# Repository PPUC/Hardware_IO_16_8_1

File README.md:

# Standard IO PCB for PPUC Project
This is the hardware for a standard IO card which was designed for the PPUC pinball project, but can be useful in other applications as well.
It is designed for being low cost and functional for experimental use.  
Not everything is tested nor does it fulfill EMC or any other specifications.  
Use at your own risk!
To make use of anything of this project a basic understanding of electronics and programming is necessary. Nothing of it is "plug and play". I'm surely not liable for any damage to assemblies, pinball machines or even persons.

## Picture of the Board

## Name
IO_16_8_1 as it has 16 inputs, 8 outputs and one special output.  
Actually the inputs can also be used as outputs (see later in this document).

## Power Supply
The IO card must be supplied by 5 V (+-0.5 V) for logic and inputs. Additionally nominal 48 V for high power outputs. As these outputs are open drain, the voltage can actually be up to 60 V. In the circuit diagram the voltage is called 48 V.

## Controller
A RP2040 is used for it's cost/performance ratio. It is the same controller that is used in the Raspberry Pi Pico.

## Communication Interfaces
* RS_485: main communication interface for controlling outputs and scan inputs. Usually connected to a host interface like a PC or Raspberry Pi or similar.
* USB C: for programming, debug and flashing
* Serial Wire: alternative for programming, debug and flashing
* IIC: the PCB can be populated with an QWIIC connector (normally not mounted). This can be used for connecting to other PCBs or experimental use. It uses the same UART as for the RS485.
* UART, I2C, SPI: instead of using the input pins for inputs they can also be used as an additional interface (see docu of RP2040 for pins and function). Speed up to 10 kHz should be possible (100 kHz for In_2 and In_3).

## Switches (on board)
* Reset: hardware reset for controller (RP2040)
* Boot: if active the board connects to a PC like an USB stick. Usually used for programming the code into the flash memory on the board.
* DIP-switches: usually used to select an address for RS485 (16 combinations)

## Inputs (and low power outputs)
The 16 inputs are used for reading the state of an external switch. The switch is normally connected to ground (GND). Internally the input is pulled up to 5 V by a 10k resistor.

All inputs can also be used as signal-outputs (if programmed accordingly). The output is internally pulled up by a 10k resistor to 5 V. A higher voltage can be applied externally (max. 30 V) but be sure to have your hardware and software! setup correctly as no protection for damage is provided in that case. A maximum of 2 mA can be sinked/sourced.

The inputs In_2 and In_3 are designed for higher speed (100 kHz). The Pull-Up can be soldered to other pads to be pulled to 3,3 V (instead of 5 V). An input capacitance can be added (soldered) for better noise immunity but lower speed. Since version 1.0.1 the caps are soldered by default and must be removed if a high-speed serial connection is needed.

The input terminals can also be "miss"used for a switch matrix. To do that (no matter if used as column or row) the input resistor (330 Ohm) must be short cut (or replaced by a zero Ohm type). Background: the 330 Ohm resistor protects the circuit if the terminal is used as an output and accidentally a short cut is done at the terminal. Unfortunately the low voltage value gets too high when used in a switch matrix (diode voltage plus voltage drop due to added up currents through the resistor). This happens when more switches are closed at the same time.  
Having said that, there is an exception: if you use the Terminals 13 to 16 (mid power) as your drivers (strobe signal) then you don't need to change anything. That gives you for example a 4x4 or 8x4 matrix. You can also always use the specially designed PCB "Hardware_IO_16x8_matrix" for your switch matrix.

The inputs In_13 to In_16 have an additional open drain output transistor that allows higher currents in case of being used as an output (up to 3 A at 25 °C ambient temperature). The outputs are internally pulled up by a 10k resistor to 5 V. A higher voltage (max. 30 V) can be applied externally but be sure to have your hardware and software! setup correctly as no protection for damage is provided in that case. Please be aware that the default state (before software takes over control) is "on".  
If used as input In_13 to In_16 feature a memory (similar to a relay self-holding function). If the input has ever seen a low signal (e.g. switch closed to GND) it will stay that way until it gets an active high signal from the RP2040 (make the corresponding pin an output with signal "high" and then make it an input again). If this behavior is not wanted you can lift pin 3 of Q13 to Q16, then you have an input/output like e.g. terminal 1 with static behavior but no additional output power.  
Why not keep it simple and make all inputs the same? To give the choice to use the terminals as outputs (mid-power) as in pinball use case, there are often too many inputs and a lack on outputs. Therefore an output transistor to 4 of the I/O pins were added to be able to switch more power. As an side effect if this terminal is configured as an input it has this memory or self-holding characteristic (once triggered stays triggered). This can be dealt with by software, in a way that it actually acts like a normal input. In the end you have the benefit of mid-power-output but the drawback that the software getting more complex for the use case of a "normal" input.  
If you use the PPUC software and you have configured the terminal as an input, it acts like a normal input and you don't have to care about it.

Here is an example what software steps are needed for normal input configuration, e.g. for IN_14:
1. find the corresponding GPIO for IN_14: that is GPIO16 at the physical Pin 27 of RP2040
2. set GPIO16 as output and set it to "high".
3. configure the GPIO16 as an input (now it is an input that is "low active", therefore setup for a switch to ground)
4. if a low at the terminal IN_14 appears, the GPIO16 will be read as "low" and stays that way even if the switch on terminal IN_14 opens again (self-holding)
5. when you think it's time to reactivate the input ("arm the input"), then goto 2.

If you do 5. always right after the input read "low" than it looks like a normal input without self-holding characteristic.

## High Power Outputs
There are 8 high power outputs available. Usually they are connected to pinball solenoids or flashers. A recovery diode for the solenoids is placed on the pcb, so no need for diodes at the coils. The outputs are open drain and drive currents up to 20 A with a load connected to a voltage of up to 60 V. Be aware that the current is limited by the fuse F2. It will blow within about 1 s at 20 A. You might use a 10 A fuse if necessary.

It's recommended to use 2 wires (back and forth) for each solenoid. That improves the EMC a lot.

## Special Output
One special output is available for high speed signals. The voltage is 5 V, it is a push pull output that can drive a current up to 8 mA. It can be used to e.g. control a WS2812 LED strip.

## Terminal Blocks, Connectors
The PCB holes are designed to take different manufacturers of 6 pin terminal blocks. Be sure to use terminal blocks with a pitch of 3.5 mm. There is some additional space at the front and back of the terminal blocks to accommodate different sizes (e.g., Dinkle and Phoenix Contact). Some no-name manufacturers from China are also already in use. The direct clamping blocks are the least expensive but please also consider using plug-in terminals for easy maintenance (see picture below).

## Recommendations
* Connect only one Flipper to a pcb if possible. The advantage is, that all the energy of the big capacitor is available for the flipper, which is usually the solenoid with the highest current. If you have more flipper fingers than PCBs then spread the flipper solenoids as even as possible across the PCBs (e.g. if you have 6 flipper fingers it's better to connect 2 per board instead of all 6 at one board).
* Wire related switches and solenoids for fast flip devices (e.g. flipper, bumper, sling, kick back) to the same pcb. Then you can archive the shortest possible time lag between activating the switch and firing the solenoid.
* RS485 termination: short JP2 at the end of the RS485 bus. There should also be a 120 Ohm resistor at the beginning of the bus (e.g. USB to RS485 adapter).
* RS485 biasing: short JP1 and JP3 exactly once at any point of the RS485 bus. Only do this if no bias resistors are installed on the USB to RS485 adapter. 
* It's recommended to use flipper coils for higher voltage (like 40 - 50 V) as they draw less current. Since Version 1.1.1 low resistance coils (designed for 24 V) should work as well. You should also change the fuse F2 to 10 A for that application.
* If the MOSFETs on the high power outputs are not available (or you want to use the big player brands) here are some alternatives (I haven't tested any of them, but they should work according to their specification): GL40N10A4 (seems to be the same as NCE0140KA), RD3P200SNFRA, NVD6824NL, IPD90N10S4L-06, LSGG10R085W3

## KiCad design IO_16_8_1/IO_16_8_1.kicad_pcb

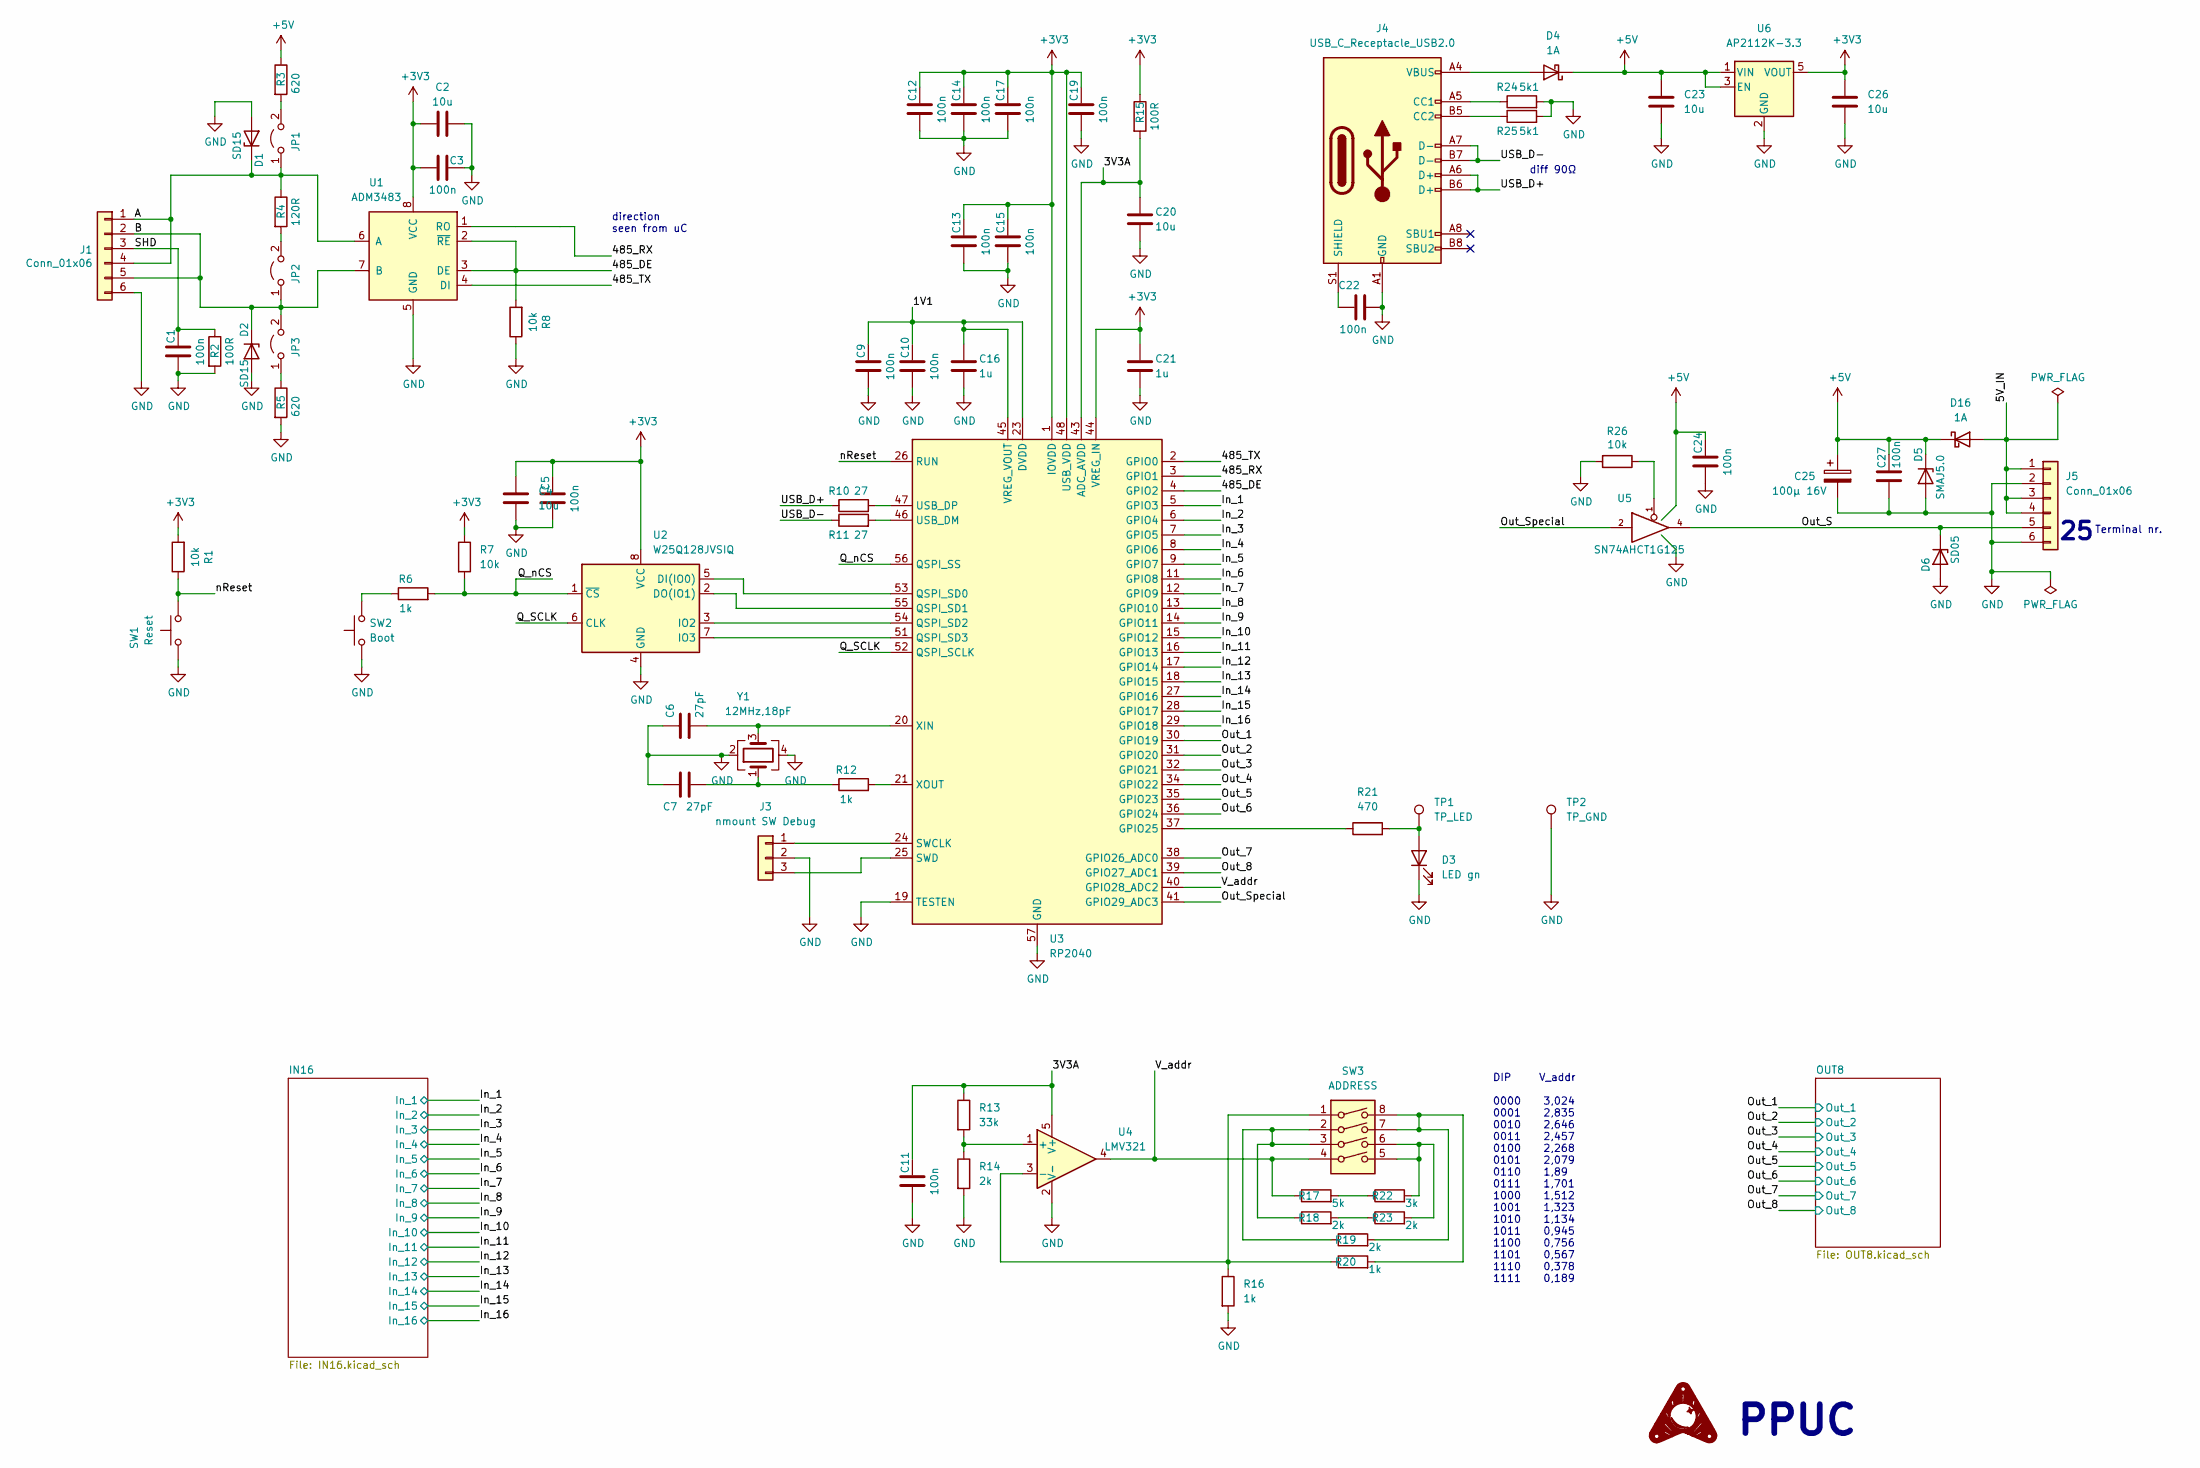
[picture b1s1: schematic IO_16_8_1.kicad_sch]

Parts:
C1, C3, C5, C9, C10, C11, C12, C13, C14, C15, C17, C19, C22, C24, C27: 100n; C_0402_1005Metric
C2, C4, C20, C23, C26: 10u; C_0603_1608Metric
C6, C7: 27pF; C_0402_1005Metric
C16, C21: 1u; C_0402_1005Metric
C25: 100µ 16V; CP_Elec_6.3x5.4; JLCPCB Rotation Offset 180
D1, D2: SD15; D_SOD-323
D3: LED gn; LED_0805_2012Metric
D4, D16: 1A; D_SOD-323
D5: SMAJ5.0; D_SMA
D6: SD05; D_SOD-323
J1, J5: Conn_01x06; Terminal_Block_RTMPin
J3: nmount SW Debug; PinSocket_1x03_P2.54mm_Vertical
J4: USB_C_Receptacle_USB2.0; USB_C_Receptacle_XKB_U262-16XN-4BVC11
JP1, JP2, JP3: Jumper_2_Open; PinHeader_1x02_P2.54mm_Vertical
R1, R7, R8, R26: 10k; R_0603_1608Metric
R2, R15: 100R; R_0603_1608Metric
R3, R5: 620; R_0402_1005Metric
R4: 120R; R_0603_1608Metric
R6, R12, R16, R20: 1k; R_0402_1005Metric
R10, R11: 27; R_0402_1005Metric
R13: 33k; R_0603_1608Metric
R14, R18, R19, R23: 2k; R_0603_1608Metric
R17: 5k; R_0603_1608Metric
R21: 470; R_0603_1608Metric
R22: 3k; R_0603_1608Metric
R24, R25: 5k1; R_0603_1608Metric
SW1: Reset; SW_SPST_SKQG_WithStem
SW2: Boot; SW_SPST_SKQG_WithStem
SW3: ADDRESS; SW_DIP_SPSTx04_Slide_6.7x11.72mm_W8.61mm_P2.54mm_LowProfile; JLCPCB Rotation Offset 90
TP1: TP_LED; Pin_D1.0mm_L10.0mm
TP2: TP_GND; Pin_D1.0mm_L10.0mm
U1: ADM3483; SOIC-8_3.9x4.9mm_P1.27mm
U2: W25Q128JVSIQ; SOIC-8_5.23x5.23mm_P1.27mm
U3: RP2040; QFN-56-1EP_7x7mm_P0.4mm_EP3.2x3.2mm; JLCPCB Rotation Offset -90
U4: LMV321; SOT-23-5
U5: SN74AHCT1G125; SOT-23-5
U6: AP2112K-3.3; SOT-23-5; JLCPCB Rotation Offset 90
Y1: 12MHz,18pF; Crystal_SMD_3225-4Pin_3.2x2.5mm

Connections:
+3V3: C2.1, C3.1, C4.1, C5.1, C12.1, C13.1, C14.1, C15.1, C17.1, C19.1, C21.1, C26.1, R1.2, R7.1, R15.1, U1.8 (VCC), U2.8 (VCC), U3.1 (IOVDD), U3.10 (IOVDD), U3.22 (IOVDD), U3.33 (IOVDD), U3.42 (IOVDD), U3.44 (VREG_IN), U3.48 (USB_VDD), U3.49 (IOVDD), U6.5 (VOUT); also elsewhere on the board
+5V: C23.1, C24.1, C25.1, C27.1, D4.1 (K), D5.1 (K), D16.1 (K), R3.1, U5.5 (VCC), U6.1 (VIN), U6.3 (EN); also elsewhere on the board
/1V1: C9.1, C10.1, C16.1, U3.23 (DVDD), U3.45 (VREG_VOUT), U3.50 (DVDD)
/3V3A: C11.1, C20.1, R13.1, R15.2, U3.43 (ADC_AVDD), U4.5 (V+)
/485_DE: R8.2, U1.2 (~RE), U1.3 (DE), U3.4 (GPIO2)
/485_RX: U1.1 (RO), U3.3 (GPIO1)
/485_TX: U1.4 (DI), U3.2 (GPIO0)
/A: D1.1 (K), J1.1, J1.4, JP1.1 (A), R4.1, U1.6 (A)
/B: D2.1 (K), J1.2, J1.5, JP2.1 (A), JP3.2 (B), U1.7 (B)
/In_1: U3.5 (GPIO3); also elsewhere on the board
/In_2: U3.6 (GPIO4); also elsewhere on the board
/In_3: U3.7 (GPIO5); also elsewhere on the board
/In_4: U3.8 (GPIO6); also elsewhere on the board
/In_5: U3.9 (GPIO7); also elsewhere on the board
/In_6: U3.11 (GPIO8); also elsewhere on the board
/In_7: U3.12 (GPIO9); also elsewhere on the board
/In_8: U3.13 (GPIO10); also elsewhere on the board
/In_9: U3.14 (GPIO11); also elsewhere on the board
/In_10: U3.15 (GPIO12); also elsewhere on the board
/In_11: U3.16 (GPIO13); also elsewhere on the board
/In_12: U3.17 (GPIO14); also elsewhere on the board
/In_13: U3.18 (GPIO15); also elsewhere on the board
/In_14: U3.27 (GPIO16); also elsewhere on the board
/In_15: U3.28 (GPIO17); also elsewhere on the board
/In_16: U3.29 (GPIO18); also elsewhere on the board
/Out_1: U3.30 (GPIO19); also elsewhere on the board
/Out_2: U3.31 (GPIO20); also elsewhere on the board
/Out_3: U3.32 (GPIO21); also elsewhere on the board
/Out_4: U3.34 (GPIO22); also elsewhere on the board
/Out_5: U3.35 (GPIO23); also elsewhere on the board
/Out_6: U3.36 (GPIO24); also elsewhere on the board
/Out_7: U3.38 (GPIO26_ADC0); also elsewhere on the board
/Out_8: U3.39 (GPIO27_ADC1); also elsewhere on the board
/Out_S: D6.1 (K), J5.5, U5.4
/Out_Special: U3.41 (GPIO29_ADC3), U5.2
/Q_SCLK: U2.6 (CLK), U3.52 (QSPI_SCLK)
/Q_nCS: R6.2, R7.2, U2.1 (~CS), U3.56 (QSPI_SS)
/SHD: C1.1, J1.3, R2.1
/USB_D+: J4.A6 (D+), J4.B6 (D+), R10.1
/USB_D-: J4.A7 (D-), J4.B7 (D-), R11.1
/V_addr: R17.1, SW3.4, U3.40 (GPIO28_ADC2), U4.4
/nReset: R1.1, SW1.2, U3.26 (RUN)
unnamed: C6.2, U3.20 (XIN), Y1.3
unnamed: C7.2, R12.1, Y1.1
unnamed: C22.1, J4.S1 (SHIELD)
unnamed: D3.2 (A), R21.2, TP1.1
unnamed: D4.2 (A), J4.A4 (VBUS), J4.A9 (VBUS), J4.B4 (VBUS), J4.B9 (VBUS)
unnamed: J3.1, U3.24 (SWCLK)
unnamed: J3.3, U3.25 (SWD)
unnamed: J4.A5 (CC1), R24.1
unnamed: J4.B5 (CC2), R25.1
unnamed: JP1.2 (B), R3.2
unnamed: JP2.2 (B), R4.2
unnamed: JP3.1 (A), R5.1
unnamed: R6.1, SW2.2
unnamed: R10.2, U3.47 (USB_DP)
unnamed: R11.2, U3.46 (USB_DM)
unnamed: R12.2, U3.21 (XOUT)
unnamed: R13.2, R14.1, U4.1 (+)
unnamed: R16.1, R20.1, SW3.1, U4.3 (-)
unnamed: R17.2, R22.1
unnamed: R18.1, R19.1, SW3.2, SW3.3
unnamed: R18.2, R23.1
unnamed: R19.2, R20.2, SW3.7, SW3.8
unnamed: R21.1, U3.37 (GPIO25)
unnamed: R22.2, R23.2, SW3.5, SW3.6
unnamed: R26.1, U5.1
unnamed: U2.2 (DO(IO1)), U3.55 (QSPI_SD1)
unnamed: U2.3 (IO2), U3.54 (QSPI_SD2)
unnamed: U2.5 (DI(IO0)), U3.53 (QSPI_SD0)
unnamed: U2.7 (IO3), U3.51 (QSPI_SD3)

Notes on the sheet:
diff 90Ω
DIP V_addr 0000 3,024 0001 2,835 0010 2,646 0011 2,457 0100 2,268 0101 2,079 0110 1,89 0111 1,701 1000 1,512 1001 1,323 1010 1,134 1011 0,945 1100 0,756 1101 0,567 1110 0,378 1111 0,189
direction seen from uC
Terminal nr.
PPUC

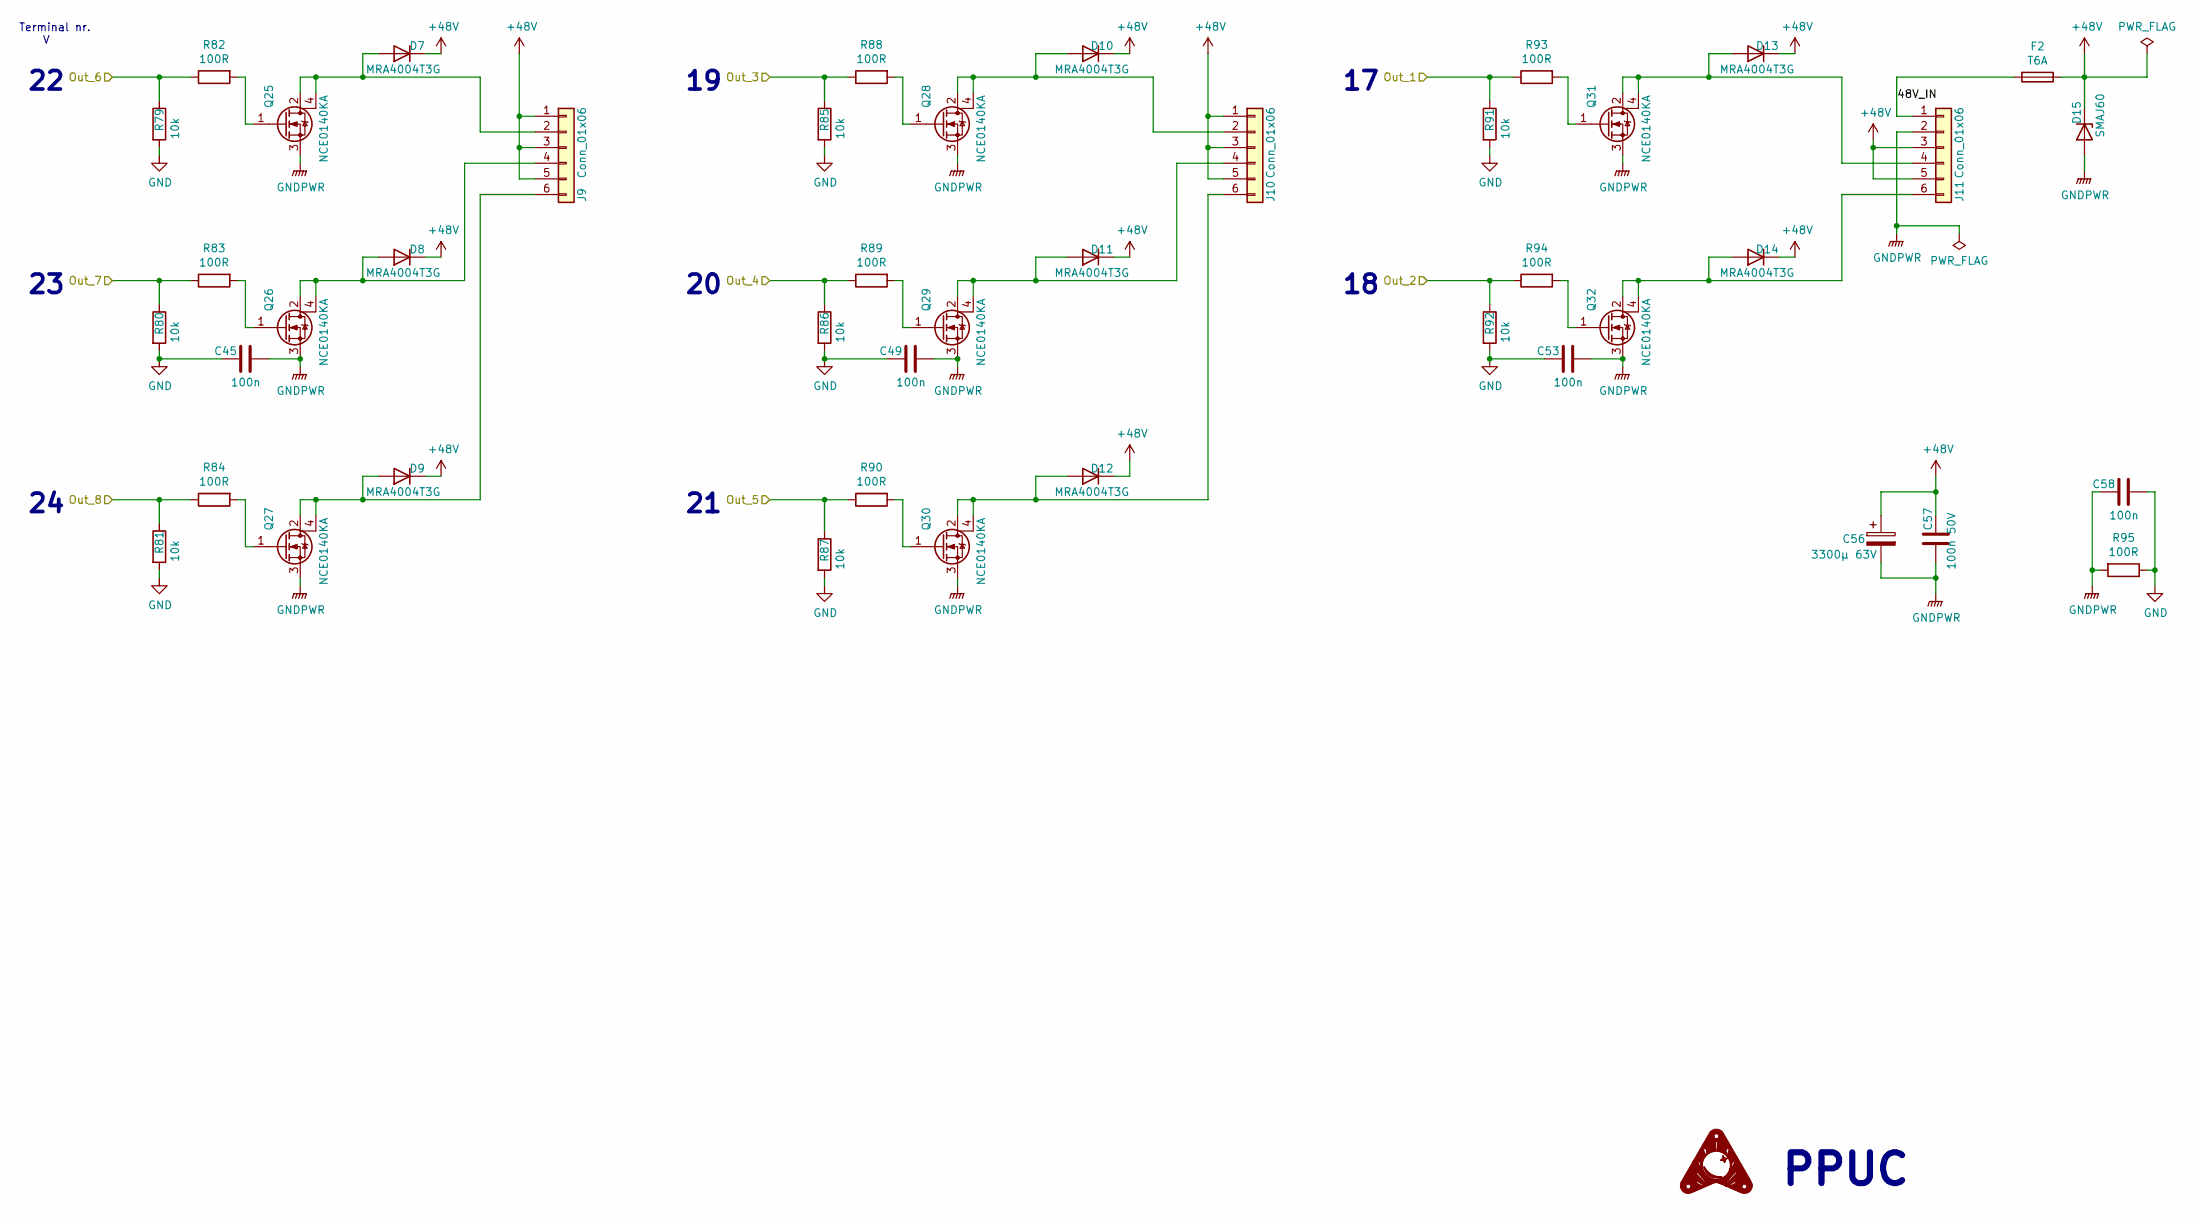
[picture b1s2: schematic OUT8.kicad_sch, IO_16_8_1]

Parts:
C45, C49, C53, C58: 100n; C_0402_1005Metric
C56: 3300µ 63V; CP_Radial_D30.0mm_P10.00mm_SnapIn
C57: 100n 50V; C_0603_1608Metric
D7, D8, D9, D10, D11, D12, D13, D14: MRA4004T3G; D_SMA
D15: SMAJ60; D_SMA
F2: T6A; Fuseholder_Cylinder-5x20mm_Schurter_0031_8201_Horizontal_Op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
J9, J10, J11: Conn_01x06; Terminal_Block_RTMPin
Q25, Q26, Q27, Q28, Q29, Q30, Q31, Q32: NCE0140KA; TO-252-3_TabPin4
R79, R80, R81, R85, R86, R87, R91, R92: 10k; R_0603_1608Metric
R82, R83, R84, R88, R89, R90, R93, R94, R95: 100R; R_0603_1608Metric

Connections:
/OUT8/48V_IN: F2.2, J11.1
/Out_1: R91.1, R93.1; also elsewhere on the board
/Out_2: R92.1, R94.1; also elsewhere on the board
/Out_3: R85.1, R88.1; also elsewhere on the board
/Out_4: R86.1, R89.1; also elsewhere on the board
/Out_5: R87.1, R90.1; also elsewhere on the board
/Out_6: R79.1, R82.1; also elsewhere on the board
/Out_7: R80.1, R83.1; also elsewhere on the board
/Out_8: R81.1, R84.1; also elsewhere on the board
unnamed: D7.2 (A), J9.2, Q25.2 (D), Q25.4 (D)
unnamed: D8.2 (A), J9.4, Q26.2 (D), Q26.4 (D)
unnamed: D9.2 (A), J9.6, Q27.2 (D), Q27.4 (D)
unnamed: D10.2 (A), J10.2, Q28.2 (D), Q28.4 (D)
unnamed: D11.2 (A), J10.4, Q29.2 (D), Q29.4 (D)
unnamed: D12.2 (A), J10.6, Q30.2 (D), Q30.4 (D)
unnamed: D13.2 (A), J11.4, Q31.2 (D), Q31.4 (D)
unnamed: D14.2 (A), J11.6, Q32.2 (D), Q32.4 (D)
unnamed: Q25.1 (G), R82.2
unnamed: Q26.1 (G), R83.2
unnamed: Q27.1 (G), R84.2
unnamed: Q28.1 (G), R88.2
unnamed: Q29.1 (G), R89.2
unnamed: Q30.1 (G), R90.2
unnamed: Q31.1 (G), R93.2
unnamed: Q32.1 (G), R94.2

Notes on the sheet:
Terminal nr. V
PPUC

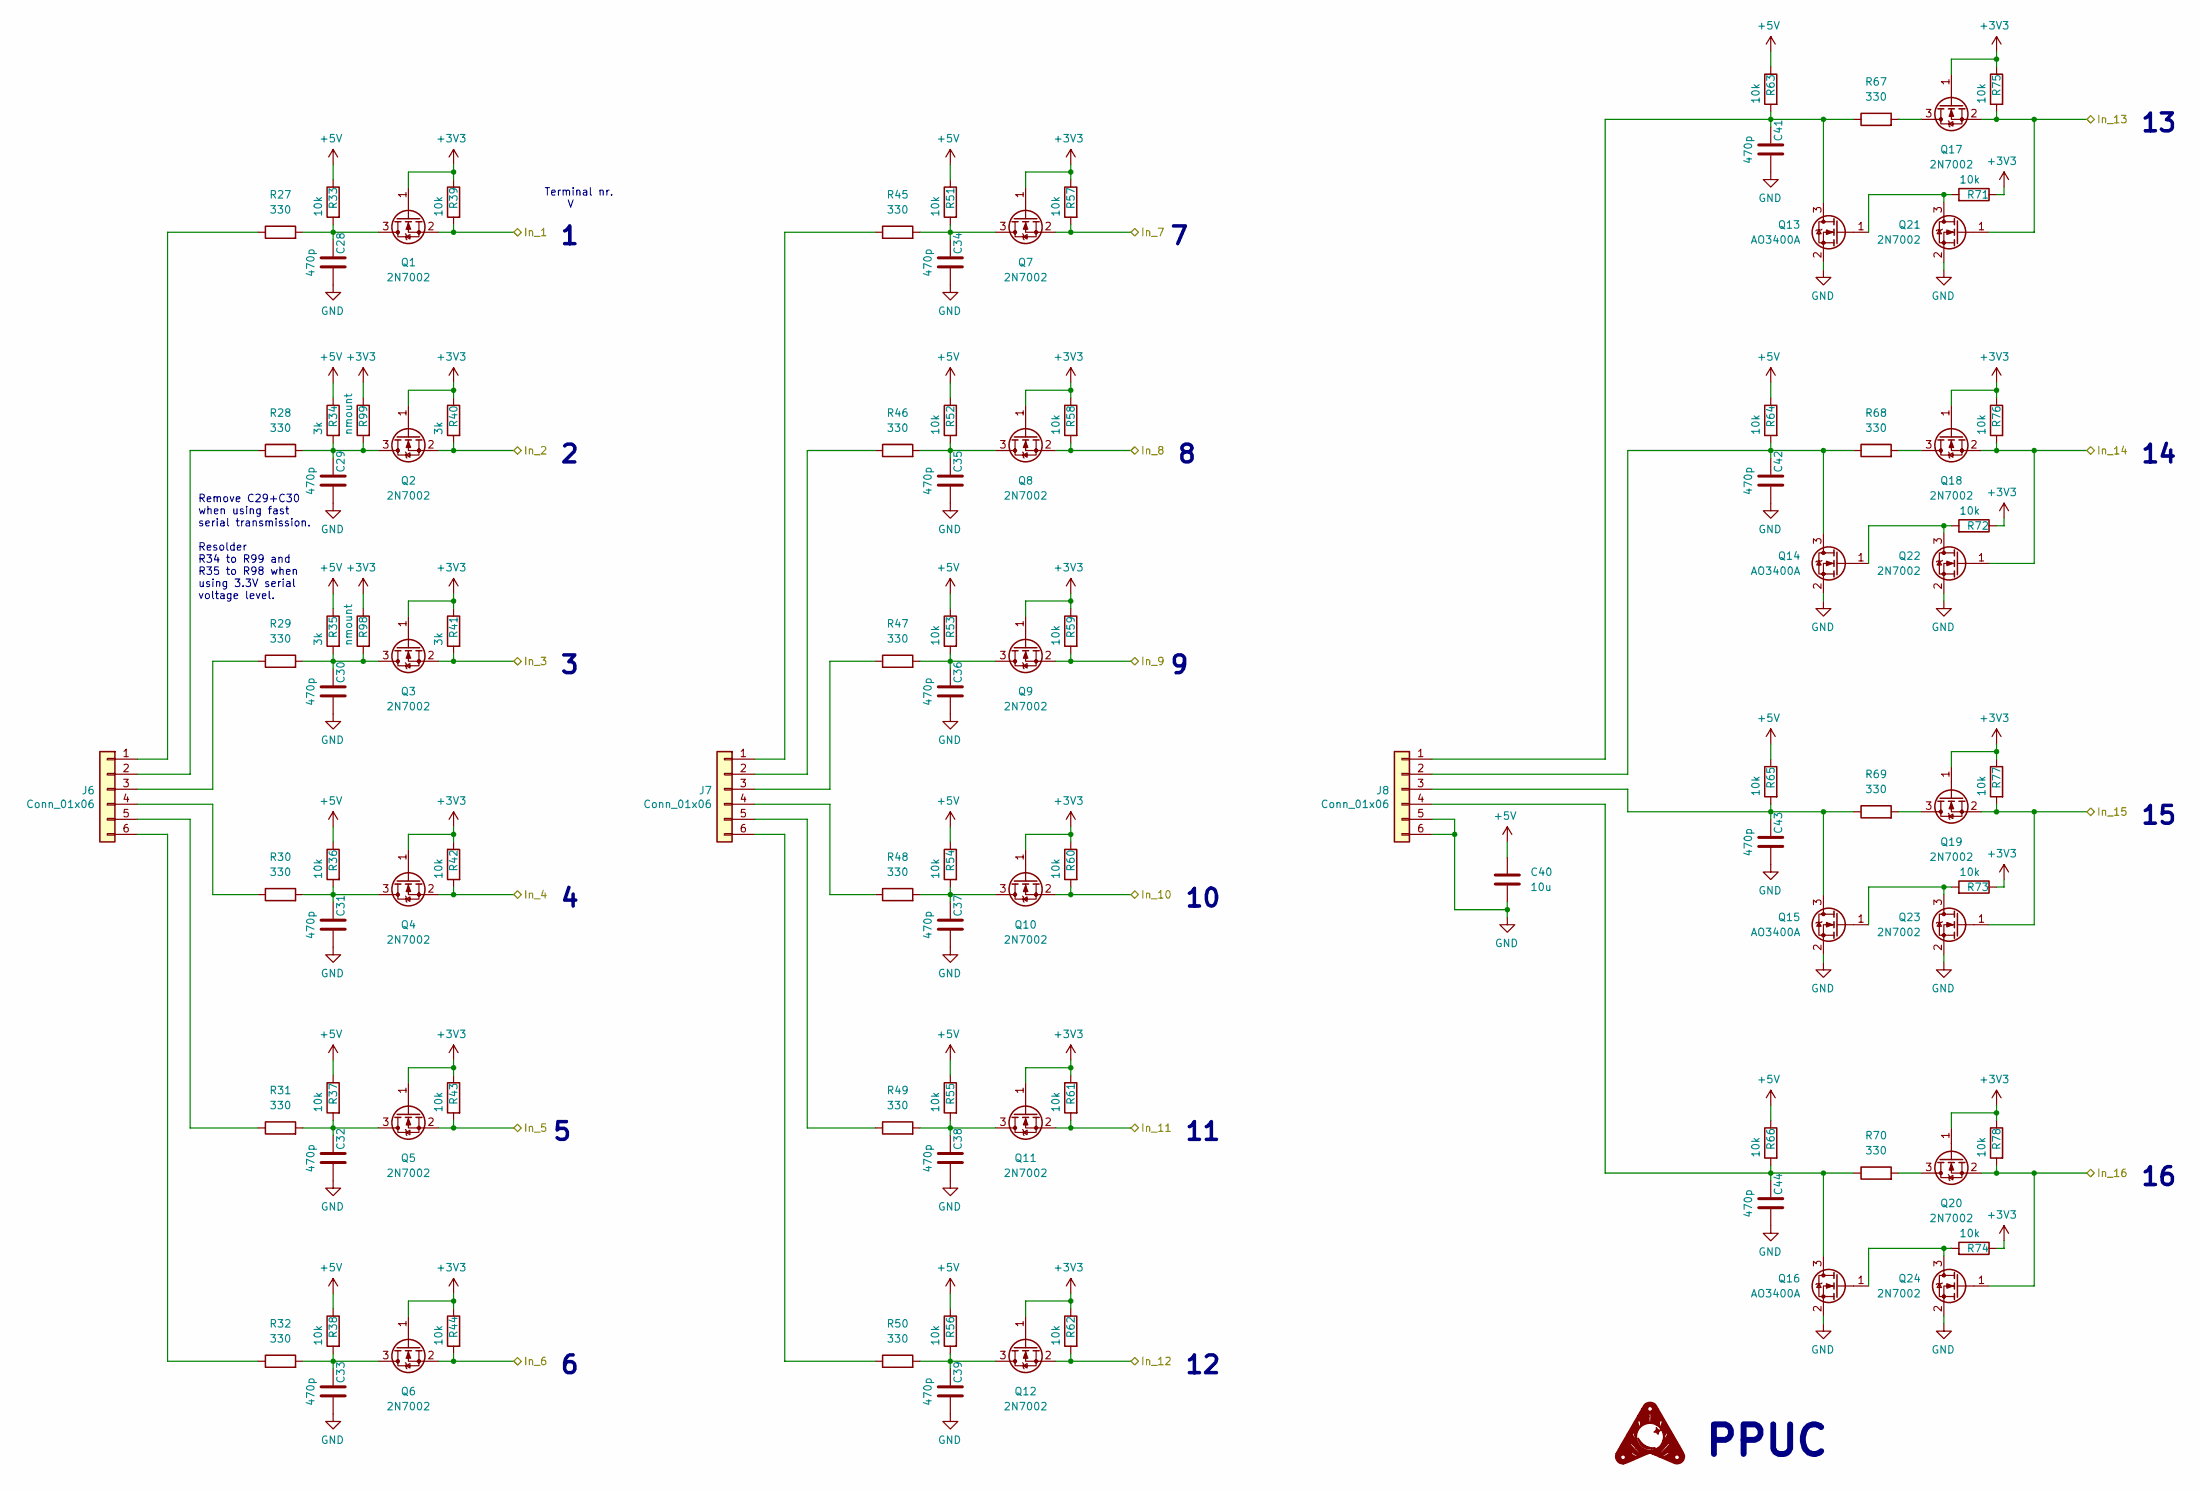
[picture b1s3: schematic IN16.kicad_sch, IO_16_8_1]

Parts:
C28, C29, C30, C31, C32, C33, C34, C35, C36, C37, C38, C39, C41, C42, C43, C44: 470p; C_0603_1608Metric
C40: 10u; C_0603_1608Metric
J6, J7, J8: Conn_01x06; Terminal_Block_RTMPin
Q1, Q2, Q3, Q4, Q5, Q6, Q7, Q8, Q9, Q10, Q11, Q12, Q17, Q18, Q19, Q20, Q21, Q22, Q23, Q24: 2N7002; SOT-23
Q13, Q14, Q15, Q16: AO3400A; SOT-23
R27, R28, R29, R30, R31, R32, R45, R46, R47, R48, R49, R50, R67, R68, R69, R70: 330; R_0603_1608Metric
R33, R36, R37, R38, R39, R42, R43, R44, R51, R52, R53, R54, R55, R56, R57, R58, R59, R60, R61, R62, R63, R64, R65, R66, R71, R72, R73, R74, R75, R76, R77, R78: 10k; R_0603_1608Metric
R34, R35, R40, R41: 3k; R_0603_1608Metric
R98, R99: nmount; R_0603_1608Metric

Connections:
+3V3: Q1.1 (G), Q2.1 (G), Q3.1 (G), Q4.1 (G), Q5.1 (G), Q6.1 (G), Q7.1 (G), Q8.1 (G), Q9.1 (G), Q10.1 (G), Q11.1 (G), Q12.1 (G), Q17.1 (G), Q18.1 (G), Q19.1 (G), Q20.1 (G), R39.1, R40.1, R41.1, R42.1, R43.1, R44.1, R57.1, R58.1, R59.1, R60.1, R61.1, R62.1, R71.1, R72.1, R73.1, R74.1, R75.1, R76.1, R77.1, R78.1, R98.1, R99.1; also elsewhere on the board
+5V: C40.1, R33.1, R34.1, R35.1, R36.1, R37.1, R38.1, R51.1, R52.1, R53.1, R54.1, R55.1, R56.1, R63.1, R64.1, R65.1, R66.1; also elsewhere on the board
/In_1: Q1.2 (S), R39.2; also elsewhere on the board
/In_2: Q2.2 (S), R40.2; also elsewhere on the board
/In_3: Q3.2 (S), R41.2; also elsewhere on the board
/In_4: Q4.2 (S), R42.2; also elsewhere on the board
/In_5: Q5.2 (S), R43.2; also elsewhere on the board
/In_6: Q6.2 (S), R44.2; also elsewhere on the board
/In_7: Q7.2 (S), R57.2; also elsewhere on the board
/In_8: Q8.2 (S), R58.2; also elsewhere on the board
/In_9: Q9.2 (S), R59.2; also elsewhere on the board
/In_10: Q10.2 (S), R60.2; also elsewhere on the board
/In_11: Q11.2 (S), R61.2; also elsewhere on the board
/In_12: Q12.2 (S), R62.2; also elsewhere on the board
/In_13: Q17.2 (S), Q21.1 (G), R75.2; also elsewhere on the board
/In_14: Q18.2 (S), Q22.1 (G), R76.2; also elsewhere on the board
/In_15: Q19.2 (S), Q23.1 (G), R77.2; also elsewhere on the board
/In_16: Q20.2 (S), Q24.1 (G), R78.2; also elsewhere on the board
unnamed: C28.1, Q1.3 (D), R27.2, R33.2
unnamed: C29.1, Q2.3 (D), R28.2, R34.2, R99.2
unnamed: C30.1, Q3.3 (D), R29.2, R35.2, R98.2
unnamed: C31.1, Q4.3 (D), R30.2, R36.2
unnamed: C32.1, Q5.3 (D), R31.2, R37.2
unnamed: C33.1, Q6.3 (D), R32.2, R38.2
unnamed: C34.1, Q7.3 (D), R45.2, R51.2
unnamed: C35.1, Q8.3 (D), R46.2, R52.2
unnamed: C36.1, Q9.3 (D), R47.2, R53.2
unnamed: C37.1, Q10.3 (D), R48.2, R54.2
unnamed: C38.1, Q11.3 (D), R49.2, R55.2
unnamed: C39.1, Q12.3 (D), R50.2, R56.2
unnamed: C41.1, J8.1, Q13.3 (D), R63.2, R67.1
unnamed: C42.1, J8.2, Q14.3 (D), R64.2, R68.1
unnamed: C43.1, J8.3, Q15.3 (D), R65.2, R69.1
unnamed: C44.1, J8.4, Q16.3 (D), R66.2, R70.1
unnamed: J6.1, R27.1
unnamed: J6.2, R28.1
unnamed: J6.3, R29.1
unnamed: J6.4, R30.1
unnamed: J6.5, R31.1
unnamed: J6.6, R32.1
unnamed: J7.1, R45.1
unnamed: J7.2, R46.1
unnamed: J7.3, R47.1
unnamed: J7.4, R48.1
unnamed: J7.5, R49.1
unnamed: J7.6, R50.1
unnamed: Q13.1 (G), Q21.3 (D), R71.2
unnamed: Q14.1 (G), Q22.3 (D), R72.2
unnamed: Q15.1 (G), Q23.3 (D), R73.2
unnamed: Q16.1 (G), Q24.3 (D), R74.2
unnamed: Q17.3 (D), R67.2
unnamed: Q18.3 (D), R68.2
unnamed: Q19.3 (D), R69.2
unnamed: Q20.3 (D), R70.2

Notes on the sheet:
PPUC
Remove C29+C30 when using fast serial transmission. Resolder R34 to R99 and R35 to R98 when using 3.3V serial voltage level.
Terminal nr. V

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
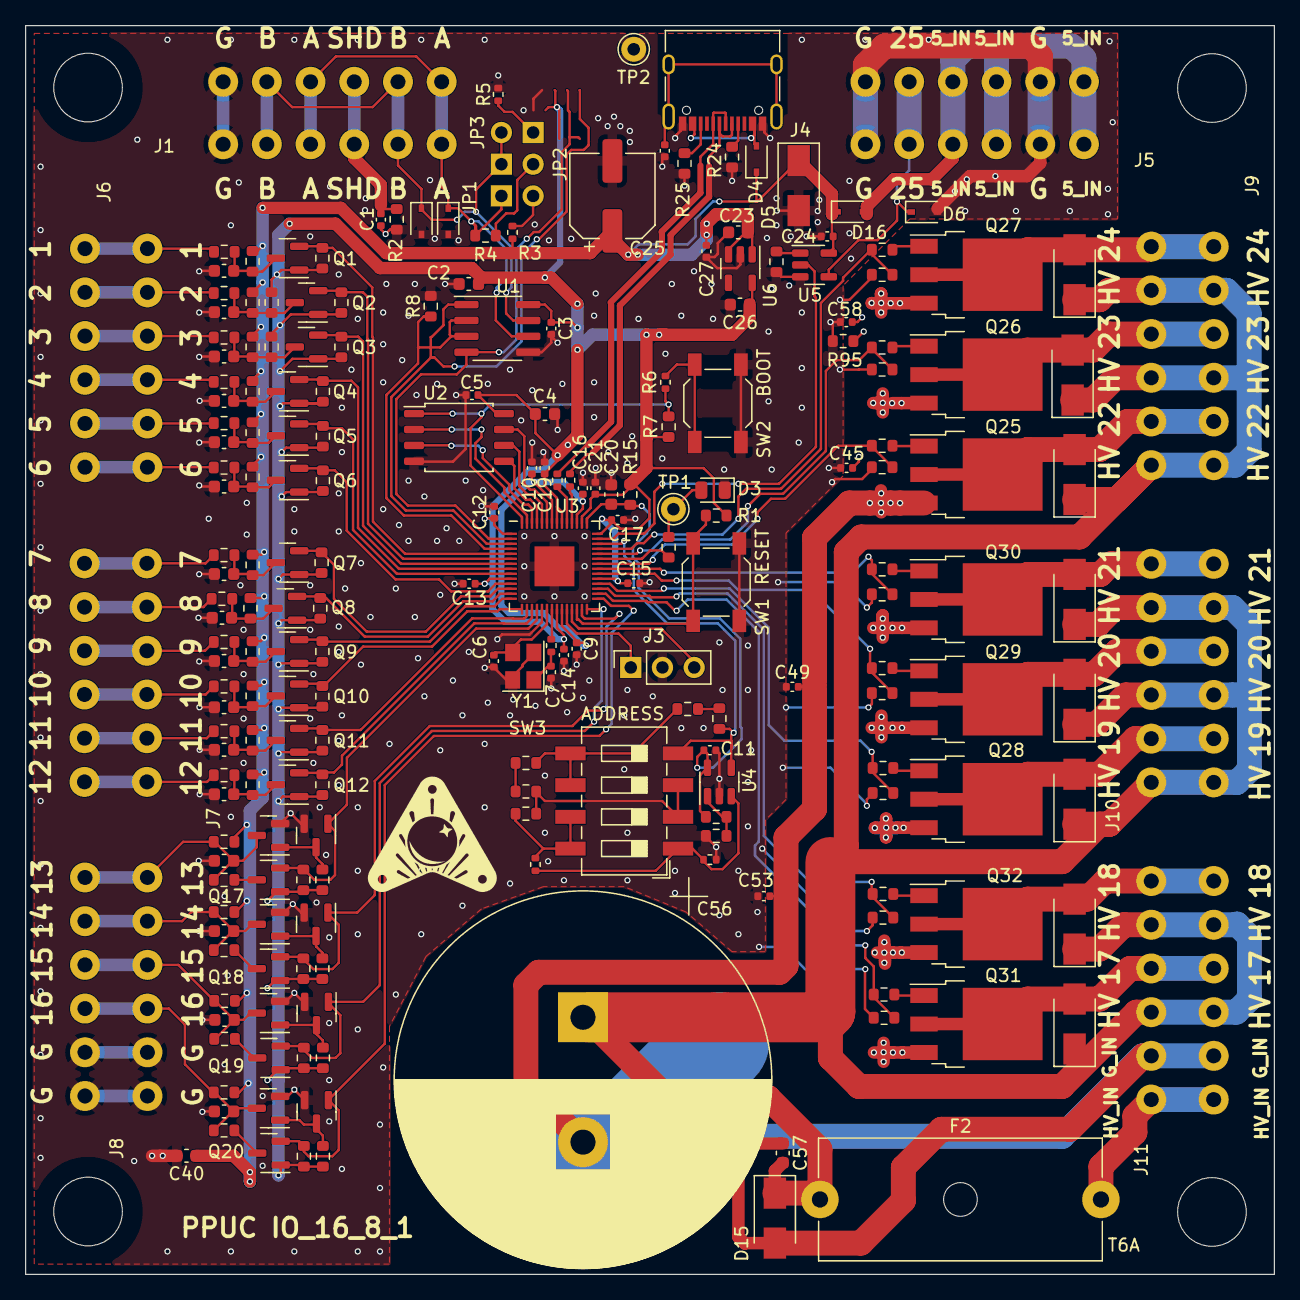
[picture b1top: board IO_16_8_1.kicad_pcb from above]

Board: 2 copper layers, 100.0 x 100.0 mm, 218 parts (0 on the bottom side), 128 nets.

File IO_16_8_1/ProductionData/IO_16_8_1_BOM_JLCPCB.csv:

Comment,Designator,Footprint,LCSC
"100n","C1,C3,C5,C8,C9,C10,C11,C12,C13,C14,C15,C17,C19,C22,C24,C27,C45,C49,C53,C58","Capacitor_SMD:C_0402_1005Metric","C1525"
"1u","C16,C21","Capacitor_SMD:C_0402_1005Metric","C52923"
"10u","C2,C4,C20,C23,C26,C40","Capacitor_SMD:C_0603_1608Metric","C19702"
"470p","C28,C29,C30,C31,C32,C33,C34,C35,C36,C37,C38,C39,C41,C42,C43,C44","Capacitor_SMD:C_0603_1608Metric","C1620"
"100n 50V","C57","Capacitor_SMD:C_0603_1608Metric","C14663"
"27pF","C6,C7","Capacitor_SMD:C_0402_1005Metric","C1557"
"SD15","D1,D2","Diode_SMD:D_SOD-323","C502529"
"SMAJ60","D15","Diode_SMD:D_SMA","C779057"
"LED gn","D3","LED_SMD:LED_0805_2012Metric","C2297"
"1A","D4","Diode_SMD:D_SOD-323","C191023"
"SMAJ5.0","D5","Diode_SMD:D_SMA","C2925443"
"SD05","D6","Diode_SMD:D_SOD-323","C2972756"
"MRA4004T3G","D7,D8,D9,D10,D11,D12,D13,D14","Diode_SMD:D_SMA","C433394"
"T500mA,<0.3Ω","F1","Fuse:Fuse_1206_3216Metric","C206993"
"USB_C_Receptacle_USB2.0","J4","Connector_USB:USB_C_Receptacle_XKB_U262-16XN-4BVC11","C709357"
"2N7002","Q1,Q2,Q3,Q4,Q5,Q6,Q7,Q8,Q9,Q10,Q11,Q12,Q17,Q18,Q19,Q20,Q21,Q22,Q23,Q24","Package_TO_SOT_SMD:SOT-23","C8545"
"AO3400A","Q13,Q14,Q15,Q16","Package_TO_SOT_SMD:SOT-23","C20917"
"IRLR3410","Q25,Q26,Q27,Q28,Q29,Q30,Q31,Q32","Package_TO_SOT_SMD:TO-252-3_TabPin4","C3017"
"10k","R1,R7,R8,R26,R33,R36,R37,R38,R39,R42,R43,R44,R51,R52,R53,R54,R55,R56,R57,R58,R59,R60,R61,R62,R63,R64,R65,R66,R71,R72,R73,R74,R75,R76,R77,R78,R79,R80,R81,R85,R86,R87,R91,R92,R96,R97","Resistor_SMD:R_0603_1608Metric","C25804"
"27","R10,R11","Resistor_SMD:R_0402_1005Metric","C138021"
"33k","R13","Resistor_SMD:R_0603_1608Metric","C4216"
"2k","R14,R18,R19,R23","Resistor_SMD:R_0603_1608Metric","C22975"
"5k","R17","Resistor_SMD:R_0603_1608Metric","C101077"
"100R","R2,R15,R82,R83,R84,R88,R89,R90,R93,R94,R95","Resistor_SMD:R_0603_1608Metric","C22775"
"470","R21","Resistor_SMD:R_0603_1608Metric","C23179"
"3k","R22,R34,R35,R40,R41","Resistor_SMD:R_0603_1608Metric","C4211"
"5k1","R24,R25","Resistor_SMD:R_0603_1608Metric","C23186"
"330","R27,R28,R29,R30,R31,R32,R45,R46,R47,R48,R49,R50,R67,R68,R69,R70","Resistor_SMD:R_0603_1608Metric","C23138"
"1k","R3,R5,R6,R12,R16,R20","Resistor_SMD:R_0402_1005Metric","C11702"
"120R","R4","Resistor_SMD:R_0603_1608Metric","C22787"
"0","R9","Resistor_SMD:R_0603_1608Metric","C21189"
"Reset","SW1","Button_Switch_SMD:SW_SPST_SKQG_WithStem","C318884"
"Boot","SW2","Button_Switch_SMD:SW_SPST_SKQG_WithStem","C318884"
"ADDRESS","SW3","Button_Switch_SMD:SW_DIP_SPSTx04_Slide_6.7x11.72mm_W8.61mm_P2.54mm_LowProfile","C54950"
"ADM3483","U1","Package_SO:SOIC-8_3.9x4.9mm_P1.27mm","C609792"
"W25Q128JVSIQ","U2","Package_SO:SOIC-8_5.23x5.23mm_P1.27mm","C97521"
"RP2040","U3","Package_DFN_QFN:QFN-56-1EP_7x7mm_P0.4mm_EP3.2x3.2mm","C2040"
"LMV321","U4","Package_TO_SOT_SMD:SOT-23-5","C7972"
"SN74AHCT1G125","U5","Package_TO_SOT_SMD:SOT-23-5","C7484"
"AP2112K-3.3","U6","Package_TO_SOT_SMD:SOT-23-5","C51118"
"12MHz,20pF","Y1","Crystal:Crystal_SMD_3225-4Pin_3.2x2.5mm","C9002"

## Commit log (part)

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2022-12-11 Readme
2022-12-11 initial version
2022-12-12 fixed typo QUIIC -> QWIIC
2022-12-14 changed In_1, In_2
2022-12-18 different pins for RS485
2022-12-30 PCB init
2023-01-05 placed out
2023-01-06 placed logic
2023-01-10 smaller Cs
2023-01-17 1/2 routed
2023-01-20 placed
2023-01-28 routed
2023-01-29 v010review
2023-02-25 v010
2023-02-26 Readme updated
2023-03-07 changed R17
2023-04-07 updated ChangeLog
2023-10-10 added pic
2023-10-21 v1.0.0
2023-11-20 readme update
2024-03-27 prod. data
2024-09-12 v101
2024-10-04 Release 1.1.0
2024-11-16 changed MOSFETs
2024-12-01 added production data
2024-12-01 corrected silk J1, J8
